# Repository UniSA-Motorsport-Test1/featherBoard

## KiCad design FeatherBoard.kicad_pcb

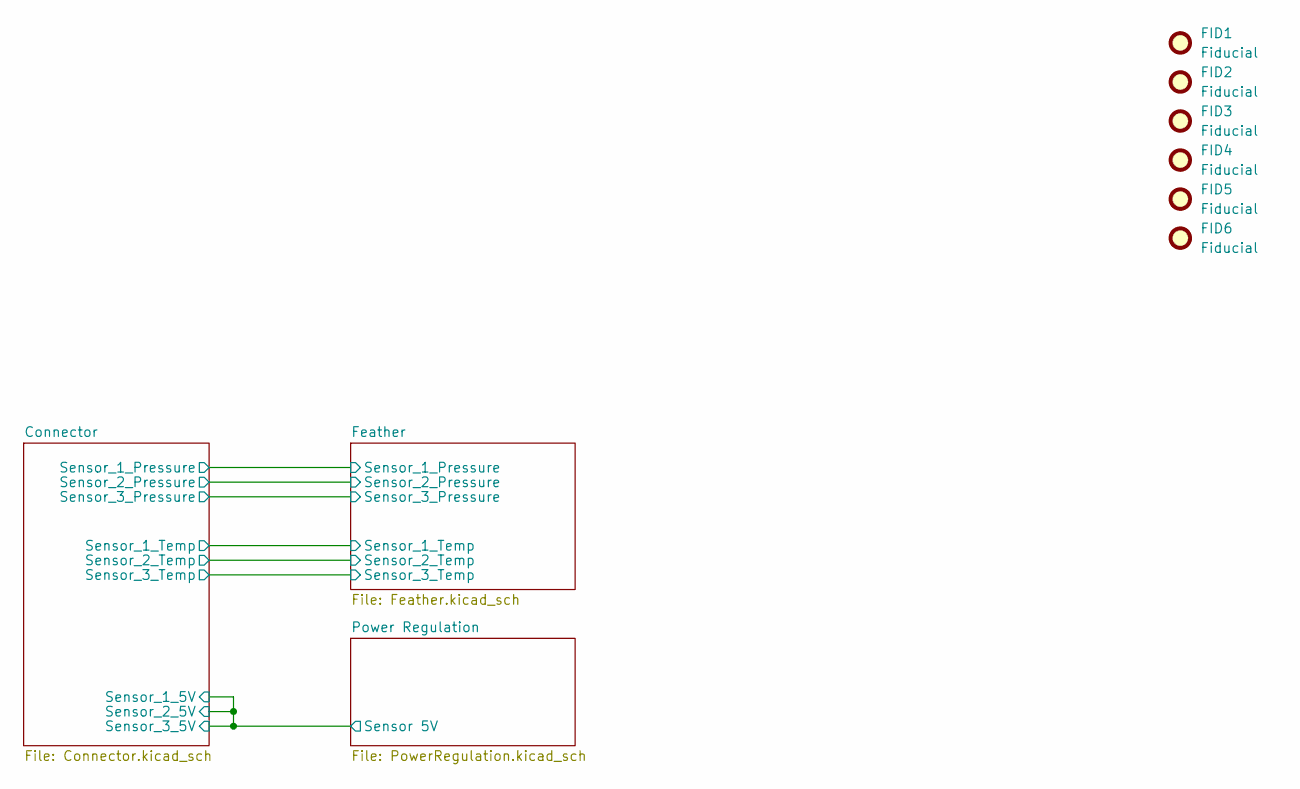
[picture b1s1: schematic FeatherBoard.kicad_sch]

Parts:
FID1, FID2, FID3, FID4, FID5, FID6: Fiducial; Fiducial_0.75mm_Mask1.5mm

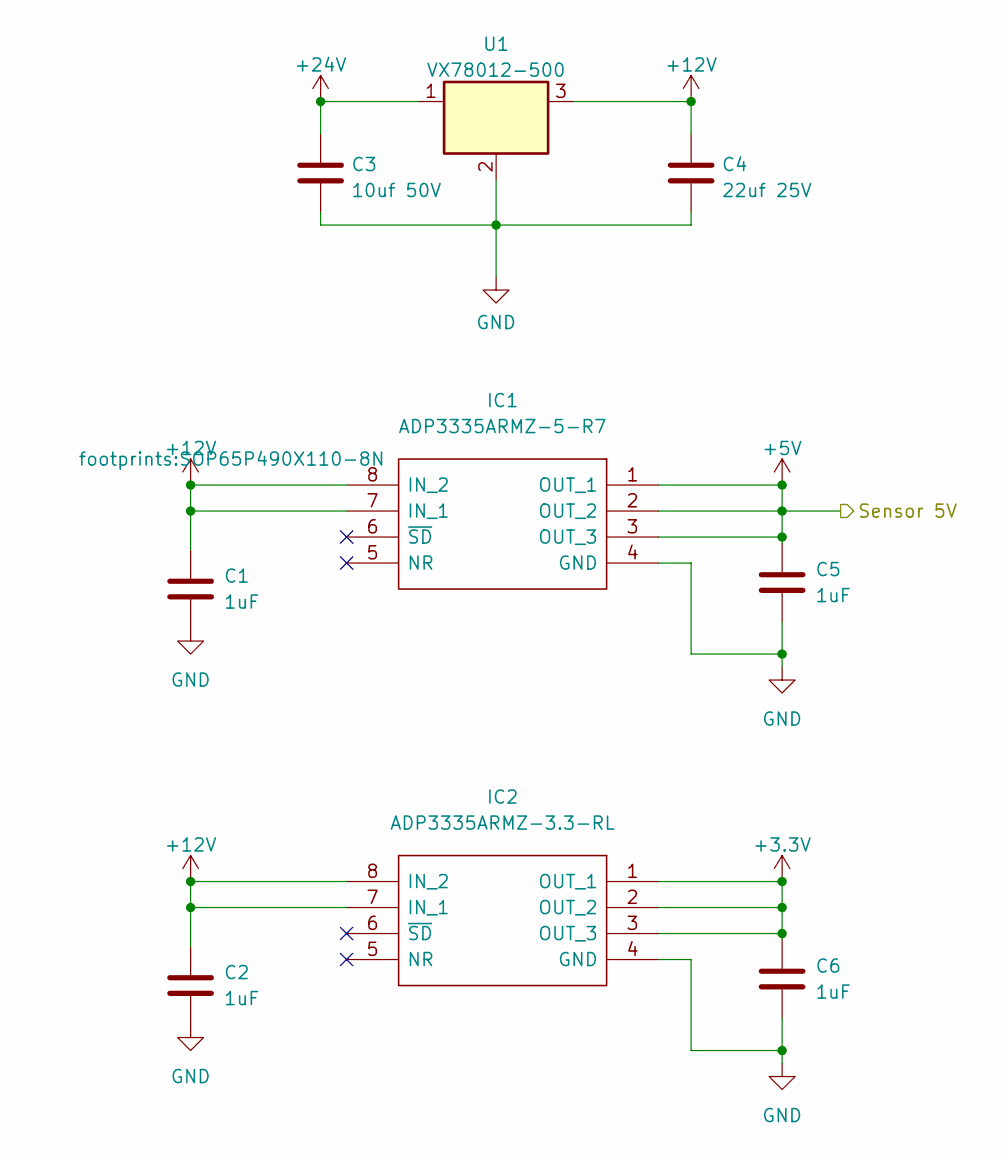
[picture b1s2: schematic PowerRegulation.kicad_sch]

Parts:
C1, C2, C5, C6: 1uF; C_0805_2012Metric
C3: 10uf 50V; C_1206_3216Metric
C4: 22uf 25V; C_1206_3216Metric
IC1: ADP3335ARMZ-5-R7; SOP65P490X110-8N; Mouser Part Number 584-ADP3335ARMZ-5-R7
IC2: ADP3335ARMZ-3.3-RL; SOP65P490X110-8N; Mouser Part Number 584-ADP3335ARMZ3.3R
U1: VX78012-500

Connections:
+3V3: C6.1, IC2.1 (OUT_1), IC2.2 (OUT_2), IC2.3 (OUT_3); also elsewhere on the board
+5V: C5.1, IC1.1 (OUT_1), IC1.2 (OUT_2), IC1.3 (OUT_3); also elsewhere on the board
+12V: C1.1, C2.1, C4.1, IC1.7 (IN_1), IC1.8 (IN_2), IC2.7 (IN_1), IC2.8 (IN_2), U1.3 (OUT)
+24V: C3.1, U1.1 (IN); also elsewhere on the board
GND: C1.2, C2.2, C3.2, C4.2, C5.2, C6.2, IC1.4 (GND), IC2.4 (GND), U1.2 (GND); also elsewhere on the board

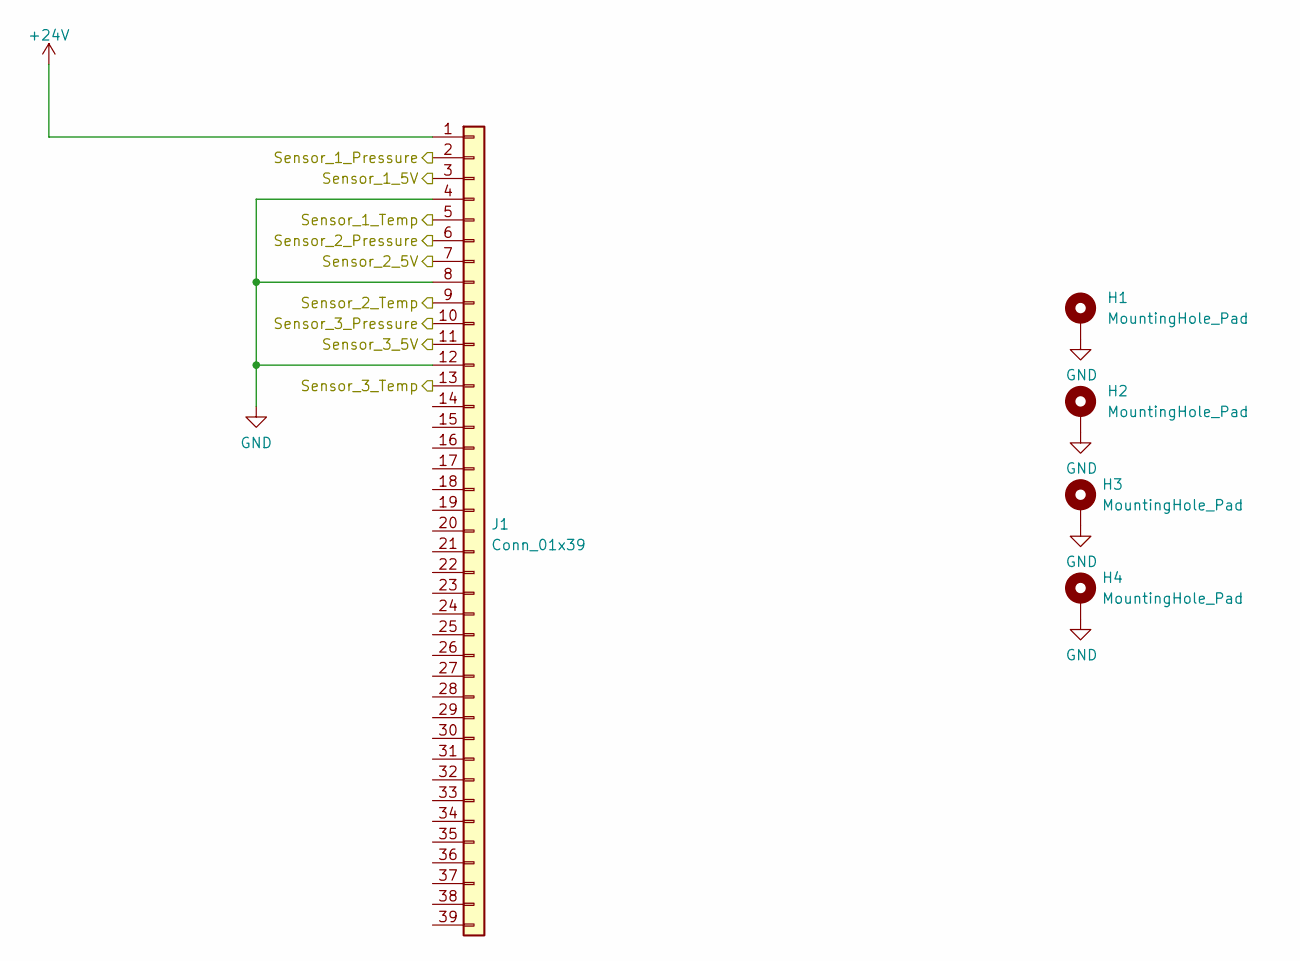
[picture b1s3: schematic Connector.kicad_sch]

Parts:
H1, H2, H3, H4: MountingHole_Pad; MountingHole_3.2mm_M3_Pad_Via
J1: Conn_01x39; Samtec_MECF-40-0_-L-DV_2x40_P1.27mm_Polarized_Edge

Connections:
+5V: J1.3, J1.7, J1.11; also elsewhere on the board
+24V: J1.1; also elsewhere on the board
/Connector/Sensor_1_Pressure: J1.2; also elsewhere on the board
/Connector/Sensor_1_Temp: J1.5; also elsewhere on the board
/Connector/Sensor_2_Pressure: J1.6; also elsewhere on the board
/Connector/Sensor_2_Temp: J1.9; also elsewhere on the board
/Connector/Sensor_3_Pressure: J1.10; also elsewhere on the board
/Connector/Sensor_3_Temp: J1.13; also elsewhere on the board
GND: H1.1, H2.1, H3.1, H4.1, J1.4, J1.8, J1.12; also elsewhere on the board

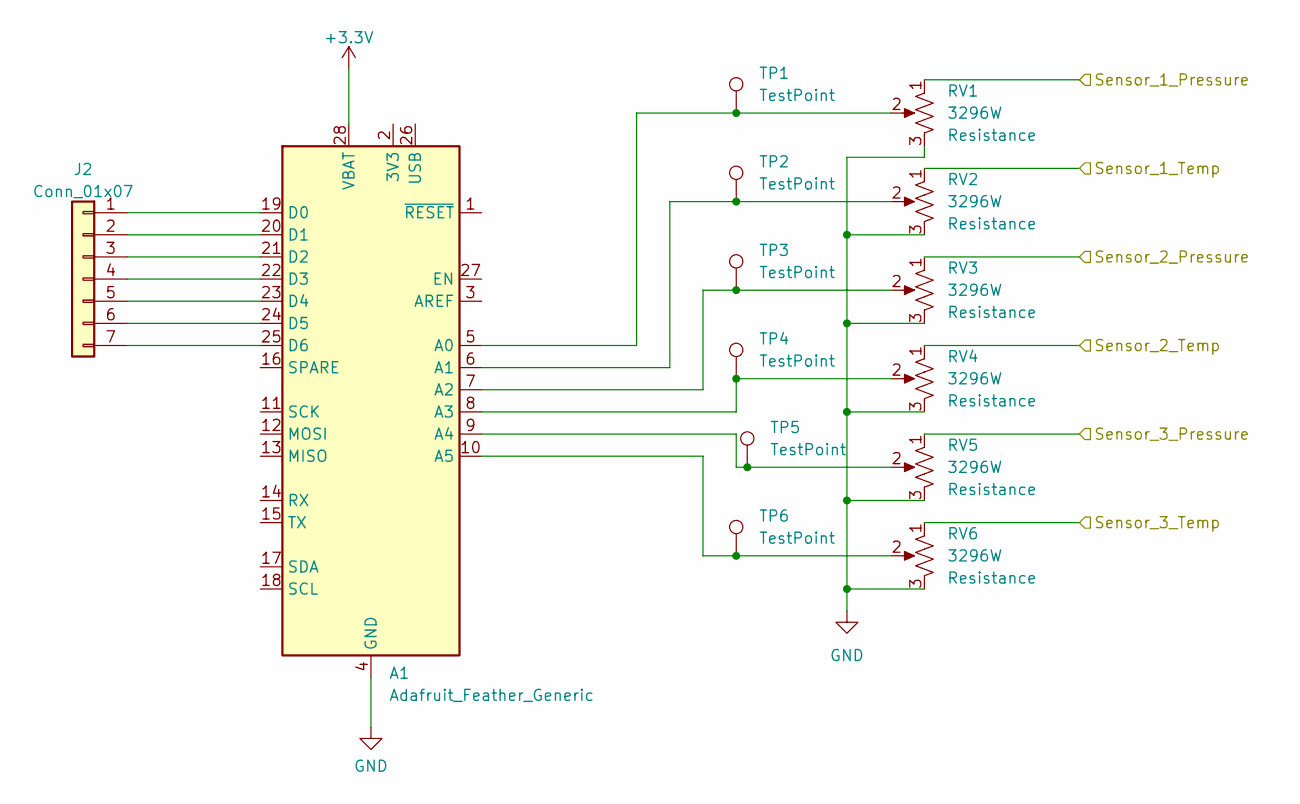
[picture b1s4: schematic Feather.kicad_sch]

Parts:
A1: Adafruit_Feather_Generic; Adafruit_Feather
J2: Conn_01x07; PinHeader_1x07_P2.54mm_Vertical
RV1, RV2, RV3, RV4, RV5, RV6: 3296W; Potentiometer_Bourns_3296W_Vertical
TP1, TP2, TP3, TP4, TP5, TP6: TestPoint; TestPoint_Loop_D2.50mm_Drill1.0mm

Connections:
+3V3: A1.28 (VBAT); also elsewhere on the board
/Connector/Sensor_1_Pressure: RV1.1; also elsewhere on the board
/Connector/Sensor_1_Temp: RV2.1; also elsewhere on the board
/Connector/Sensor_2_Pressure: RV3.1; also elsewhere on the board
/Connector/Sensor_2_Temp: RV4.1; also elsewhere on the board
/Connector/Sensor_3_Pressure: RV5.1; also elsewhere on the board
/Connector/Sensor_3_Temp: RV6.1; also elsewhere on the board
GND: A1.4 (GND), RV1.3, RV2.3, RV3.3, RV4.3, RV5.3, RV6.3; also elsewhere on the board
unnamed: A1.5 (A0), RV1.2, TP1.1
unnamed: A1.6 (A1), RV2.2, TP2.1
unnamed: A1.7 (A2), RV3.2, TP3.1
unnamed: A1.8 (A3), RV4.2, TP4.1
unnamed: A1.9 (A4), RV5.2, TP5.1
unnamed: A1.10 (A5), RV6.2, TP6.1
unnamed: A1.19 (D0), J2.1
unnamed: A1.20 (D1), J2.2
unnamed: A1.21 (D2), J2.3
unnamed: A1.22 (D3), J2.4
unnamed: A1.23 (D4), J2.5
unnamed: A1.24 (D5), J2.6
unnamed: A1.25 (D6), J2.7

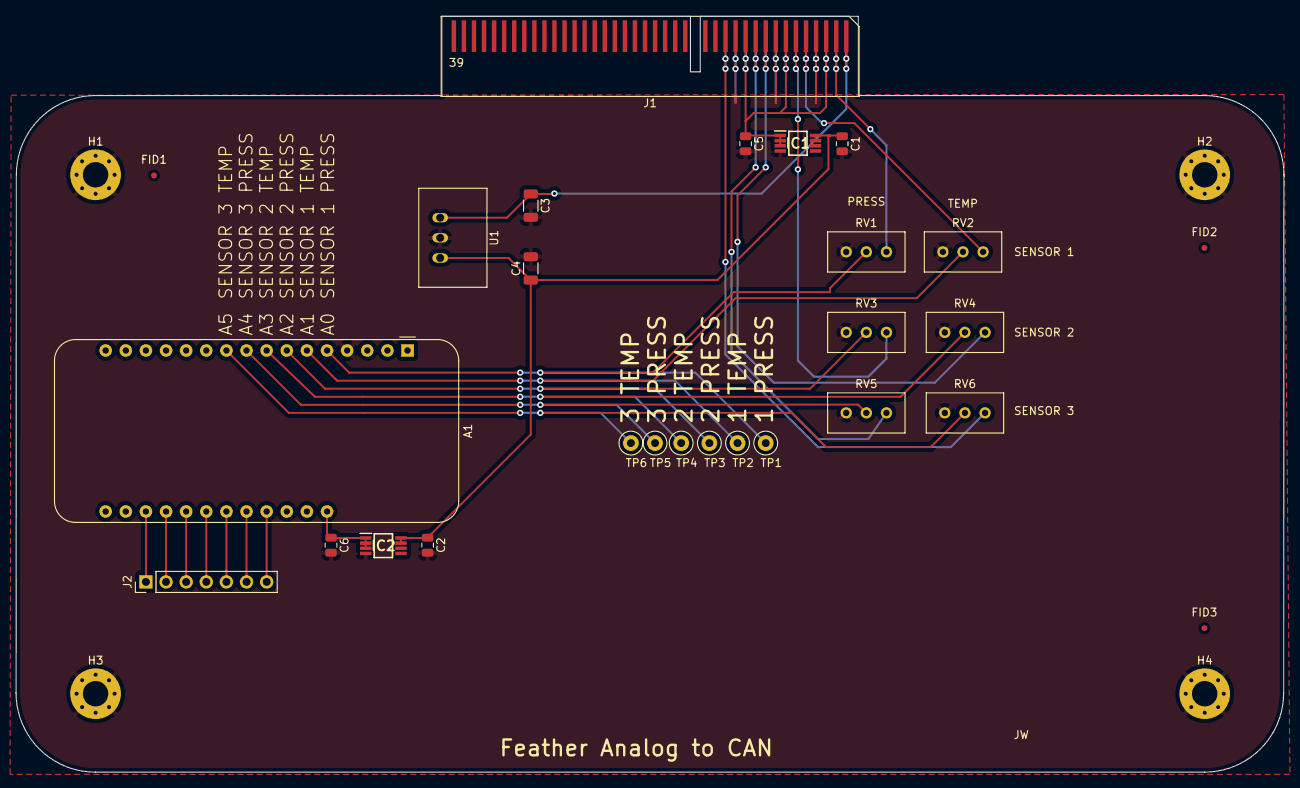
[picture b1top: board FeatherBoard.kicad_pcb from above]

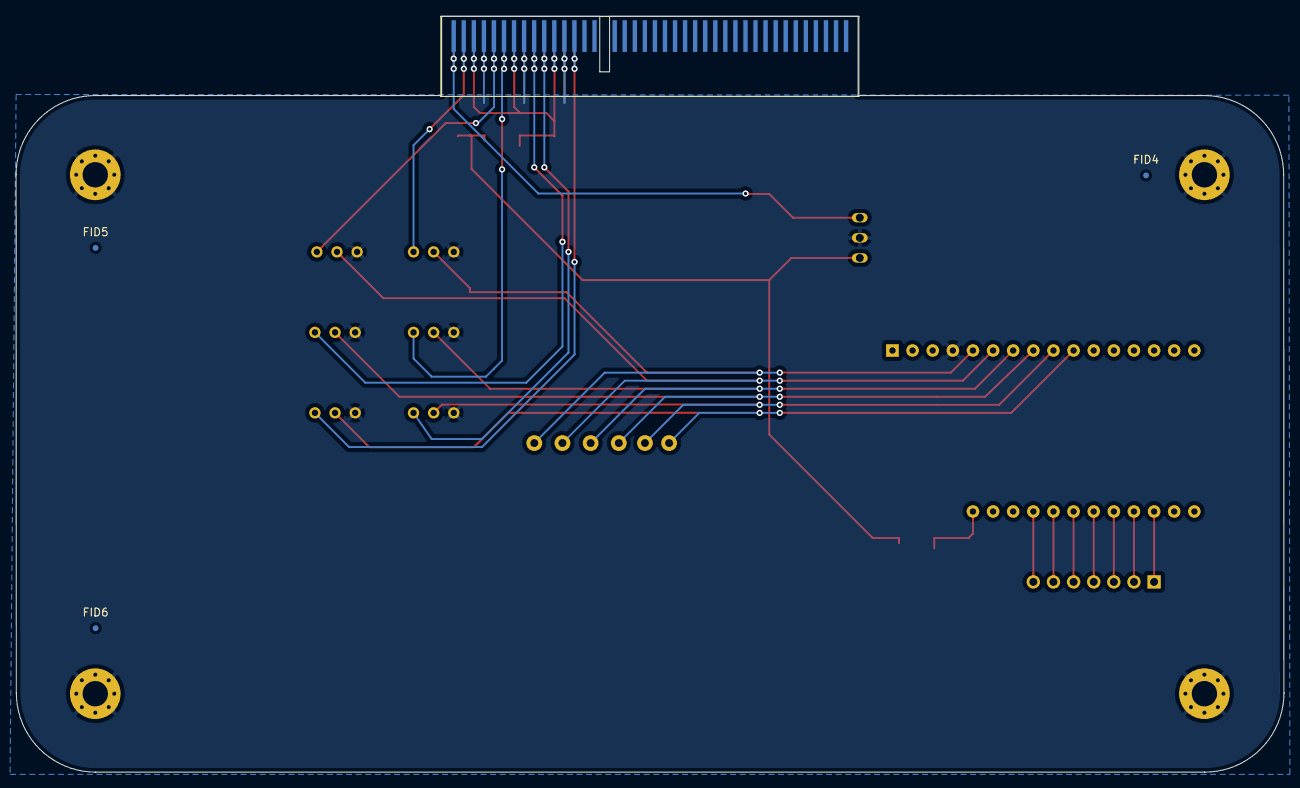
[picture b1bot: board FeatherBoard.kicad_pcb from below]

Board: 2 copper layers, 160.0 x 95.4 mm, 34 parts (3 on the bottom side), 24 nets.

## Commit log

2024-02-01 all files
